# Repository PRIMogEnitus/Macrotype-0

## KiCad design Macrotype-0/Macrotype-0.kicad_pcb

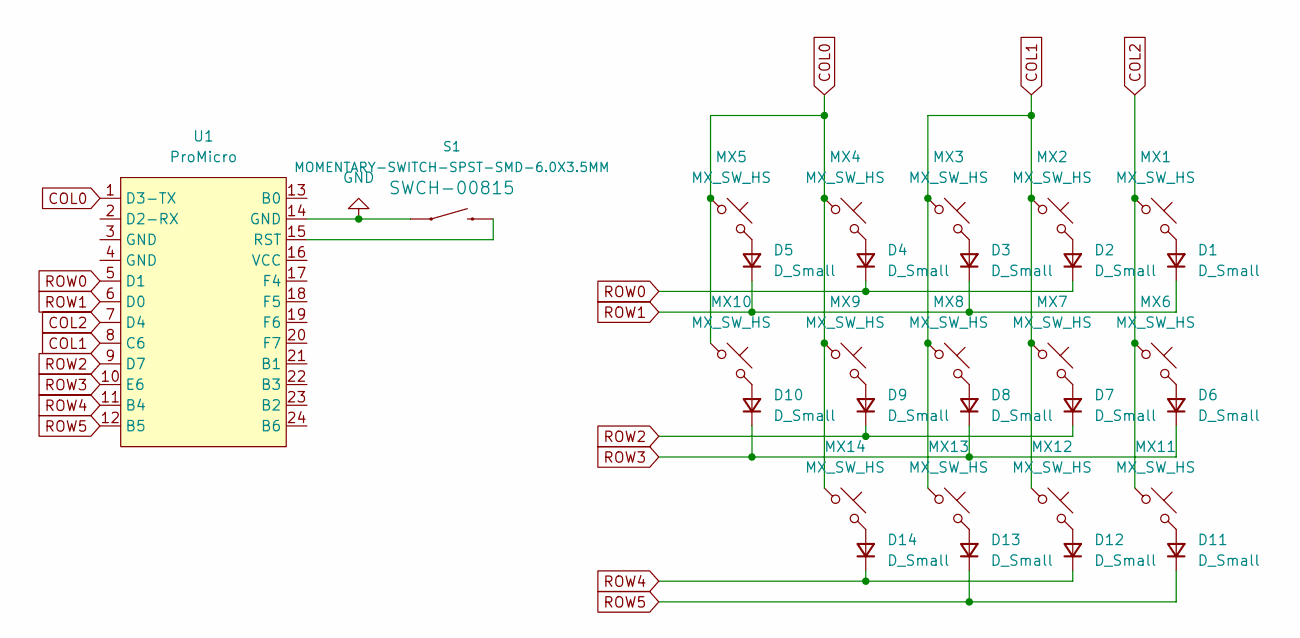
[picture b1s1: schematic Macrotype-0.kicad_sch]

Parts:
D1, D2, D3, D4, D5, D6, D7, D8, D9, D10, D11, D12, D13, D14: D_Small; D_SOD-123
MX1, MX2, MX3, MX4, MX5, MX6, MX7, MX8, MX9, MX10, MX11, MX12, MX13, MX14: MX_SW_HS; SW_MX_HS_1u
S1: MOMENTARY-SWITCH-SPST-SMD-6.0X3.5MM; TACTILE_SWITCH_SMD_6.0X3.5MM
U1: ProMicro; ProMicro_USBup

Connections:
COL0: MX4.1, MX5.1, MX9.1, MX10.1, MX14.1, U1.1 (D3-TX)
COL1: MX2.1, MX3.1, MX7.1, MX8.1, MX12.1, MX13.1, U1.8 (C6)
COL2: MX1.1, MX6.1, MX11.1, U1.7 (D4)
GND: S1.1, U1.14 (GND)
unnamed: D1.2 (A), MX1.2
unnamed: D2.2 (A), MX2.2
unnamed: D3.2 (A), MX3.2
unnamed: D4.2 (A), MX4.2
unnamed: D5.2 (A), MX5.2
unnamed: D6.2 (A), MX6.2
unnamed: D7.2 (A), MX7.2
unnamed: D8.2 (A), MX8.2
unnamed: D9.2 (A), MX9.2
unnamed: D10.2 (A), MX10.2
unnamed: D11.2 (A), MX11.2
unnamed: D12.2 (A), MX12.2
unnamed: D13.2 (A), MX13.2
unnamed: D14.2 (A), MX14.2
unnamed: S1.2, U1.15 (RST)
ROW0: D2.1 (K), D4.1 (K), U1.5 (D1)
ROW1: D1.1 (K), D3.1 (K), D5.1 (K), U1.6 (D0)
ROW2: D7.1 (K), D9.1 (K), U1.9 (D7)
ROW3: D6.1 (K), D8.1 (K), D10.1 (K), U1.10 (E6)
ROW4: D12.1 (K), D14.1 (K), U1.11 (B4)
ROW5: D11.1 (K), D13.1 (K), U1.12 (B5)

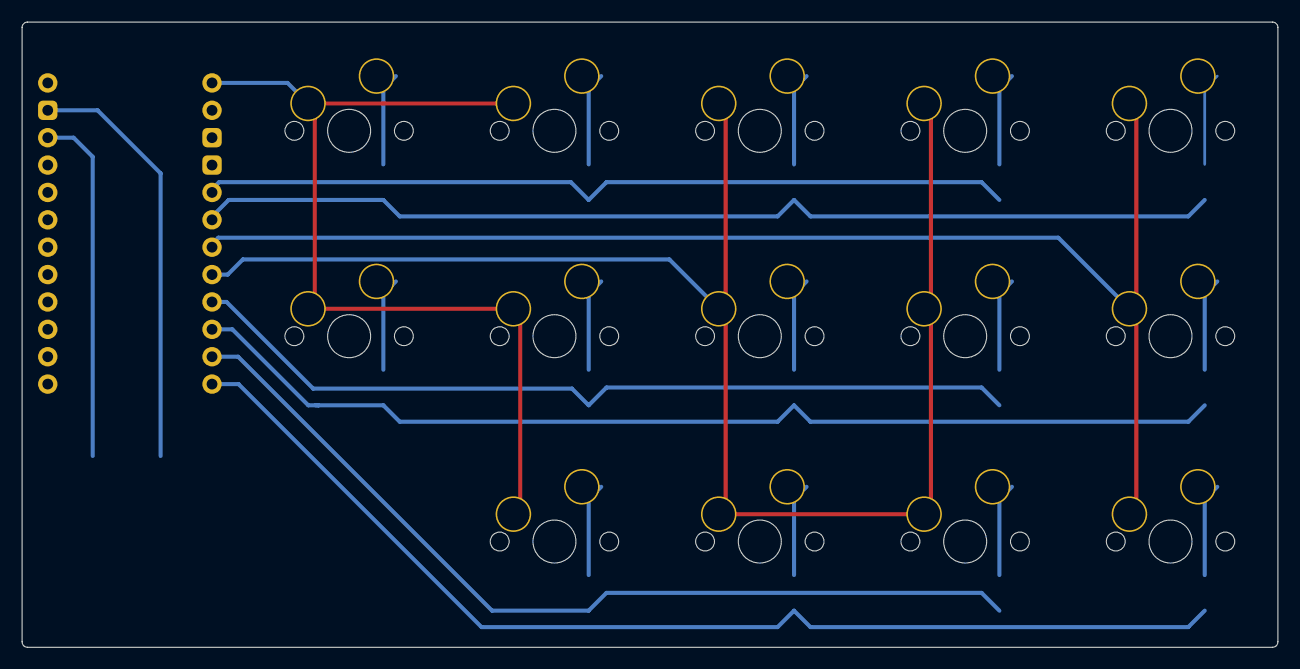
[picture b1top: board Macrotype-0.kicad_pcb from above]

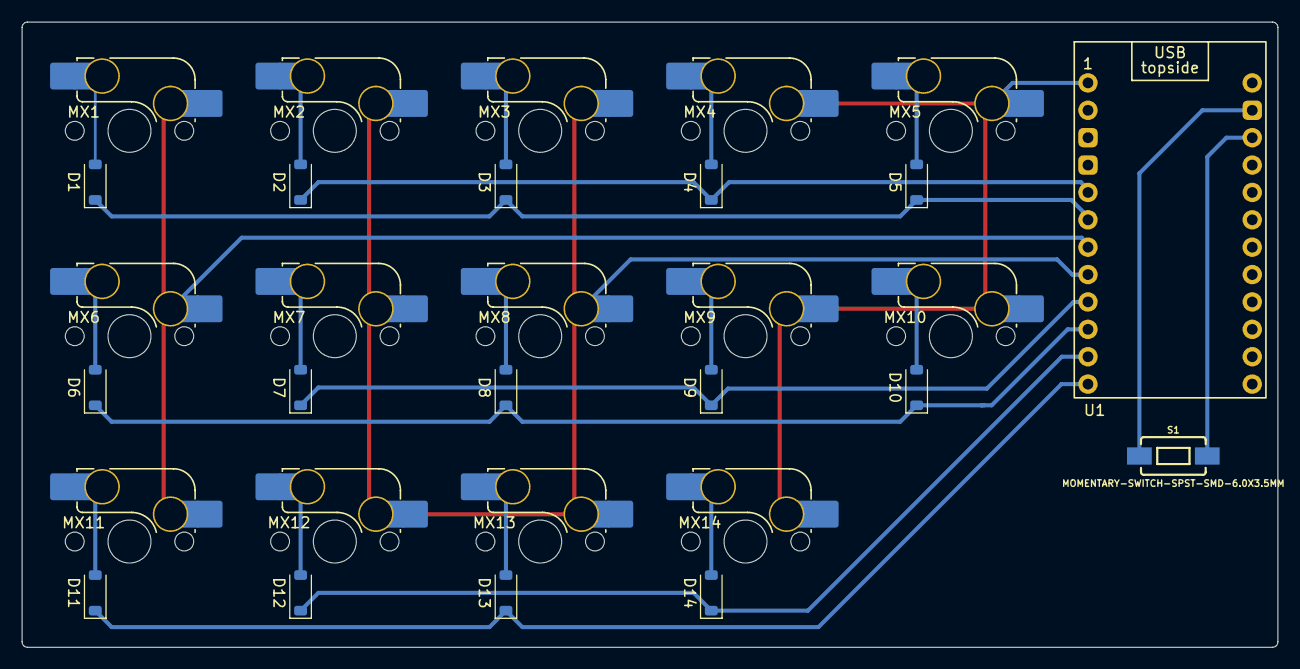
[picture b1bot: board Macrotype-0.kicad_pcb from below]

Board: 2 copper layers, 116.5 x 58.0 mm, 30 parts (30 on the bottom side), 25 nets.

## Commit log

2023-12-06 Initialization
